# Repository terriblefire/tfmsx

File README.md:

# TFMSX

A homebrew MSX2 machine using as many of the original chips as possible, with custom CPLD logic to implement the MSX slot system, memory mapper, and bus interface.

## Discord

Join the TF discord for help 

https://discord.gg/Q5zfusgnmH 

## Overview

TFMSX is an open-source hardware implementation of the MSX2 standard that combines authentic MSX chips (VDP, PSG, CPU) with modern programmable logic. The design uses a Xilinx XC95288XL CPLD to handle:

- MSX slot system (4 primary slots + secondary slot expansion)
- Memory mapper (512KB SRAM organized as 32 pages of 16KB)
- I/O address decoding and bus arbitration
- Clock generation and distribution
- Real-time clock (RP5C01A) interface

## Features

- **MSX2 Compatible**: Full MSX2 slot architecture with expansion capability
- **Original Components**: Uses genuine Yamaha V9958 VDP, YM2149 PSG, Z80 CPU
- **512KB RAM**: Memory mapper providing 32 banks of 16KB
- **Real-time Clock**: RP5C01A battery-backed RTC
- **Expansion Slots**: Support for cartridges and expansion boards
- **Multiple Revisions**: Hardware evolved through rev0 → rev1 → rev2 with improvements
- **Comprehensive Testing**: Automated test suite with CI/CD integration

## Hardware Revisions

The current repository contains the **Rev 2** design (see `boards/tfmsxr2/`), which includes:

- Improved audio output and PSG interface
- VDP reset control
- SRAM write enable (SWR pin)
- Fixed WAIT signal generation for proper Z80 timing
- Corrected slot select logic

Previous hardware revisions (Rev 0, Rev 1) are documented in the Eagle design files under `eagle/tfmsx_rev*.brd/sch`.

## Repository Structure

```
tfmsx/
├── rtl/                    # Verilog RTL source code
│   ├── tfmsx_top.v        # Top-level CPLD module
│   ├── clocks.v           # Clock generation (CPU, PSG, slot clocks)
│   └── rp5c01a.v          # Real-time clock module
├── boards/                 # Board-specific build configurations
│   ├── tfmsxr2/           # Revision 2 board (current)
│   ├── Makefile.cpld      # Common CPLD build rules
│   ├── Makefile.inc       # Docker/Xilinx environment setup
│   └── boards.txt         # List of board configurations
├── testsuite/             # Verification test benches
│   ├── bus/               # Bus interface tests (SRAM, ROM, VDP, PSG, slots)
│   │   ├── test_sram_access.v    # SRAM read/write tests
│   │   ├── test_rom_access.v     # ROM access tests
│   │   ├── test_vdp_io.v         # VDP I/O tests
│   │   ├── test_psg_io.v         # PSG I/O tests
│   │   ├── test_slot_access.v    # Slot system tests
│   │   ├── bus_fixture.vinc      # Common test fixture
│   │   ├── bus_tasks.vinc        # Reusable bus cycle tasks
│   │   └── Makefile              # Test build rules
│   ├── rtl/               # Simulation support files (Xilinx primitives)
│   ├── clocks.vinc        # Clock generation for tests
│   ├── unittest.vinc      # Test assertion macros
│   └── Makefile.inc       # Common test environment setup
├── eagle/                 # Eagle CAD hardware designs
│   ├── tfmsx.sch/.brd     # Main board schematic and layout
│   ├── extract_bom.py     # BOM extraction script
│   └── Makefile           # Automated Gerber/PDF/BOM generation
├── roms/                  # MSX system ROM tools
│   ├── Makefile           # Automated ROM download and assembly
│   └── makedefaultroms.sh # Legacy script (deprecated)
└── .github/workflows/        # CI/CD automation
    ├── run-tests.yml         # Automated test execution
    ├── gerbers.yml           # Gerber file generation
    ├── schematic-pdf.yml     # PDF schematic generation
    └── generate_assembly.yml # BOM and CPL generation
```

## Building the CPLD Firmware

### Prerequisites

- **Linux**: Xilinx ISE 10.1 installed at `/opt/Xilinx/10.1/`
- **macOS/Windows**: Docker (automatically builds and uses container)

The build system automatically handles Docker on non-Linux platforms.

### Build All Boards

```bash
cd boards
make all
```

This compiles CPLD firmware for all boards listed in `boards/boards.txt` and generates `.jed` JEDEC programming files.

### Build Specific Board

```bash
cd boards/tfmsxr2
make
```

Output: `tfmsxr2_top.jed` (JEDEC programming file) and `tfmsxr2_top.svf` (Serial Vector Format)

### Clean Build Artifacts

```bash
cd boards
make clean       # Remove intermediate build files
make distclean   # Remove all generated files including .jed
```

### Create Release Package

```bash
cd boards
make zip
```

Generates: `tfmsx_YYYY_MM_DD_<git-hash>.zip` containing all board `.jed` files.

## Programming the CPLD

Flash the CPLD using xc3sprog with an FT232H-based programmer:

```bash
cd boards/tfmsxr2
make flash
```

This requires:
- xc3sprog tool installed
- FT232H USB programmer connected
- Proper JTAG connections to the XC95288XL

## MSX System ROMs

The `roms/` directory contains a Makefile to download and prepare MSX2 system ROMs for use with the TFMSX hardware.

### Building System ROMs

```bash
cd roms
make           # Download ROMs and create default.rom
make -j8       # Parallel download (faster)
make clean     # Remove all generated files
```

The Makefile automatically downloads MSX2 BIOS ROMs from the BlueMSX emulator repository and creates a combined ROM image with multiple banks:

- **Bank 0**: MSX2 (Standard) + MSX2EXT + DISK ROM
- **Bank 1**: MSX2BR (Brazilian) + MSX2BREXT + DISK ROM
- **Bank 2**: MSX2P (MSX2+) + MSX2PEXT + DISK ROM
- **Bank 3**: MSX2SP (Spanish MSX2+) + MSX2SPEXT + DISK ROM

The final output is `default.rom`, which contains all four banks concatenated together. This allows the TFMSX hardware to support multiple MSX2 configurations by bank switching.

**Features**:
- Dependency tracking: Only downloads missing files
- Incremental builds: Only rebuilds changed targets
- Parallel downloads: Use `-j` flag for faster downloads
- Clean target: Easy cleanup with `make clean`

**Note**: These ROMs are copyrighted by their respective manufacturers. Only links are provided. 

## Technical Details

### Memory Map

| Address Range | Function |
|---------------|----------|
| 0x0000-0x3FFF | Page 0 (slot configurable) |
| 0x4000-0x7FFF | Page 1 (slot configurable) |
| 0x8000-0xBFFF | Page 2 (slot configurable) |
| 0xC000-0xFFFF | Page 3 (slot configurable) |

Each page can be mapped to any of 4 slots via the slot register (I/O port 0xA8).

### I/O Port Map

| Port(s) | Device | Function |
|---------|--------|----------|
| 0x98-0x9B | VDP | Yamaha V9958 Video Display Processor |
| 0xA0-0xA3 | PSG | Yamaha YM2149 Programmable Sound Generator |
| 0xA8-0xAB | PPI | 8255 Programmable Peripheral Interface (slot register) |
| 0xB4 | RTC | RP5C01A address latch |
| 0xB5 | RTC | RP5C01A data register |
| 0xFC-0xFF | Mapper | Memory mapper page registers (32 banks × 16KB) |

### Clock Frequencies

- **Master Clock**: 28 MHz (crystal oscillator)
- **CPU Clock (CLKCPU)**: 3.5 MHz (÷8)
- **PSG Clock (PSGCLK)**: 1.75 MHz (÷16)
- **Slot Clock (SLOTCLK)**: 3.5 MHz (÷8)

### CPLD Resources

- **Target Device**: Xilinx XC95288XL-10-TQ144
- **Macrocells**: 288
- **Package**: 144-pin TQFP
- **Speed Grade**: -10 (100 MHz)

Utilization varies by revision but typically uses 70-85% of available macrocells.

## Testing

The `testsuite/` directory contains Verilog testbenches for verifying CPLD functionality. Tests use Icarus Verilog for simulation.

### Running Tests

```bash
cd testsuite/bus
make              # Run all tests
make clean        # Clean generated files
```

### Test Coverage

The test suite includes comprehensive coverage of bus operations:

- **test_sram_access.v**: SRAM read/write operations, chip select timing, mapper control
- **test_rom_access.v**: ROM output enable, address decoding, data bus behavior
- **test_vdp_io.v**: VDP I/O ports (0x98-0x9B), read/write signals, timing
- **test_psg_io.v**: PSG I/O ports (0xA0-0xA2), control signals
- **test_slot_access.v**: MSX slot system, memory mapping, slot registers (0xA8, 0xFC-0xFF)

Each test verifies:
- Correct signal timing and activation
- Proper address decoding
- Bus protocol compliance
- Memory/peripheral access patterns

Tests automatically generate waveform files (`.vcd`) for debugging.

### Continuous Integration

All tests run automatically on push via GitHub Actions. Test status is visible in the badge at the top of this README.

## Development Workflow

1. **Modify RTL**: Edit Verilog files in `rtl/`
2. **Run Tests**: `cd testsuite/bus && make` to verify changes (see [Testing](#testing) section)
3. **Build CPLD**: `cd boards/tfmsxr2 && make`
4. **Flash Hardware**: `make flash` (if hardware available)
5. **Test on Hardware**: Verify functionality on physical board

## VDP Configuration

The TFMSX board supports both V9938 and V9958 video display processors. The VDP chip type is selected using jumpers JP3 and JP4. The CPLD automatically handles all other configuration differences.

### Jumper Settings

| VDP Chip | JP3 (Single Position) | JP4 (Two Position) |
|----------|----------------------|-------------------|
| **V9938** | **Closed** | **Left Position** |
| **V9958** | **Open** | **Right Position** |

**Jumper Types**:
- **JP3**: Single position jumper - either closed (jumper installed) or open (no jumper)
- **JP4**: Two position jumper - set to either left or right position

**Configuration Summary**:
- **V9938**: JP3 closed, JP4 left position
- **V9958**: JP3 open, JP4 right position

The CPLD logic uses these jumper settings to configure timing and control signals appropriately for the installed VDP chip.

## Hardware Design Files

Eagle CAD schematics and board layouts are in `eagle/`:

- **Main Board**: `tfmsx.sch` / `tfmsx.brd` (Rev 2 - current design)
- **Previous Revisions**: `tfmsx_rev0.*`, `tfmsx_rev1.*` (historical reference)

### Generating Gerber Files

The `eagle/` directory includes a Makefile for automated Gerber generation using Docker (no Eagle installation required).

```bash
cd eagle
make               # Generate Gerbers for main TFMSX board
make pdf           # Generate PDF schematic for main board
make bom           # Generate Bill of Materials (BOM) CSV
make cpl           # Generate Component Placement List (CPL) CSV
make assembly      # Generate both BOM and CPL for assembly
```

Output files are named with git commit hash and date (e.g., `tfmsx_a1b2c3d_2025_11_14.zip`).

**Requirements**:
- Docker with `terriblefire78/eagle:v1` and `terriblefire78/eagle-pdf` images (for gerbers and PDF)
- Python 3 (for BOM/CPL generation)

### Assembly Files (BOM and CPL)

Generate assembly files for PCB fabrication and assembly:

```bash
cd eagle
make assembly      # Generate both BOM and CPL
```

This creates two files for JLCPCB/PCBA services:

**BOM (`tfmsx_bom.csv`)** contains:
- **Comment**: Component value/part number
- **Designator**: Reference designators (e.g., C1, C2, R5)
- **Footprint**: PCB footprint package
- **LCSC Part #**: LCSC/JLCPCB part number (if available)

**CPL (`tfmsx_cpl.csv`)** contains:
- **Designator**: Component reference
- **Mid X, Mid Y**: Component center position in mm
- **Layer**: Top or Bottom
- **Rotation**: Component rotation in degrees

The BOM groups identical components together for easy ordering and assembly.

## Contributing

This is an open hardware project. Contributions welcome for:

- RTL improvements and optimizations
- Additional test coverage (please include tests for new features)
- Hardware revision suggestions
- Documentation enhancements
- Bug fixes

When contributing RTL changes, please ensure all tests pass by running `cd testsuite/bus && make`.

## License

This work is licensed under the Creative Commons Attribution-NoDerivatives 4.0 International License.

Copyright (c) 2021-2025 Stephen J. Leary

You are free to:
- **Share** - copy and redistribute the material in any medium or format for any purpose, even commercially

Under the following terms:
- **Attribution** - You must give appropriate credit, provide a link to the license, and indicate if changes were made
- **NoDerivatives** - If you remix, transform, or build upon the material, you may not distribute the modified material

See the [LICENSE](LICENSE) file for the complete license text, or visit:
https://creativecommons.org/licenses/by-nd/4.0/

## References

- [MSX Technical Documentation](https://www.msx.org/)
- [MSX Resource Center](https://www.msx.org/wiki/)
- MSX2 Technical Handbook
- Z80 CPU User Manual
- [Yamaha V9958 VDP Documentation](https://www.msx.org/wiki/Yamaha_V9958)

## Contact

For questions, issues, or contributions, please use the GitHub issue tracker.

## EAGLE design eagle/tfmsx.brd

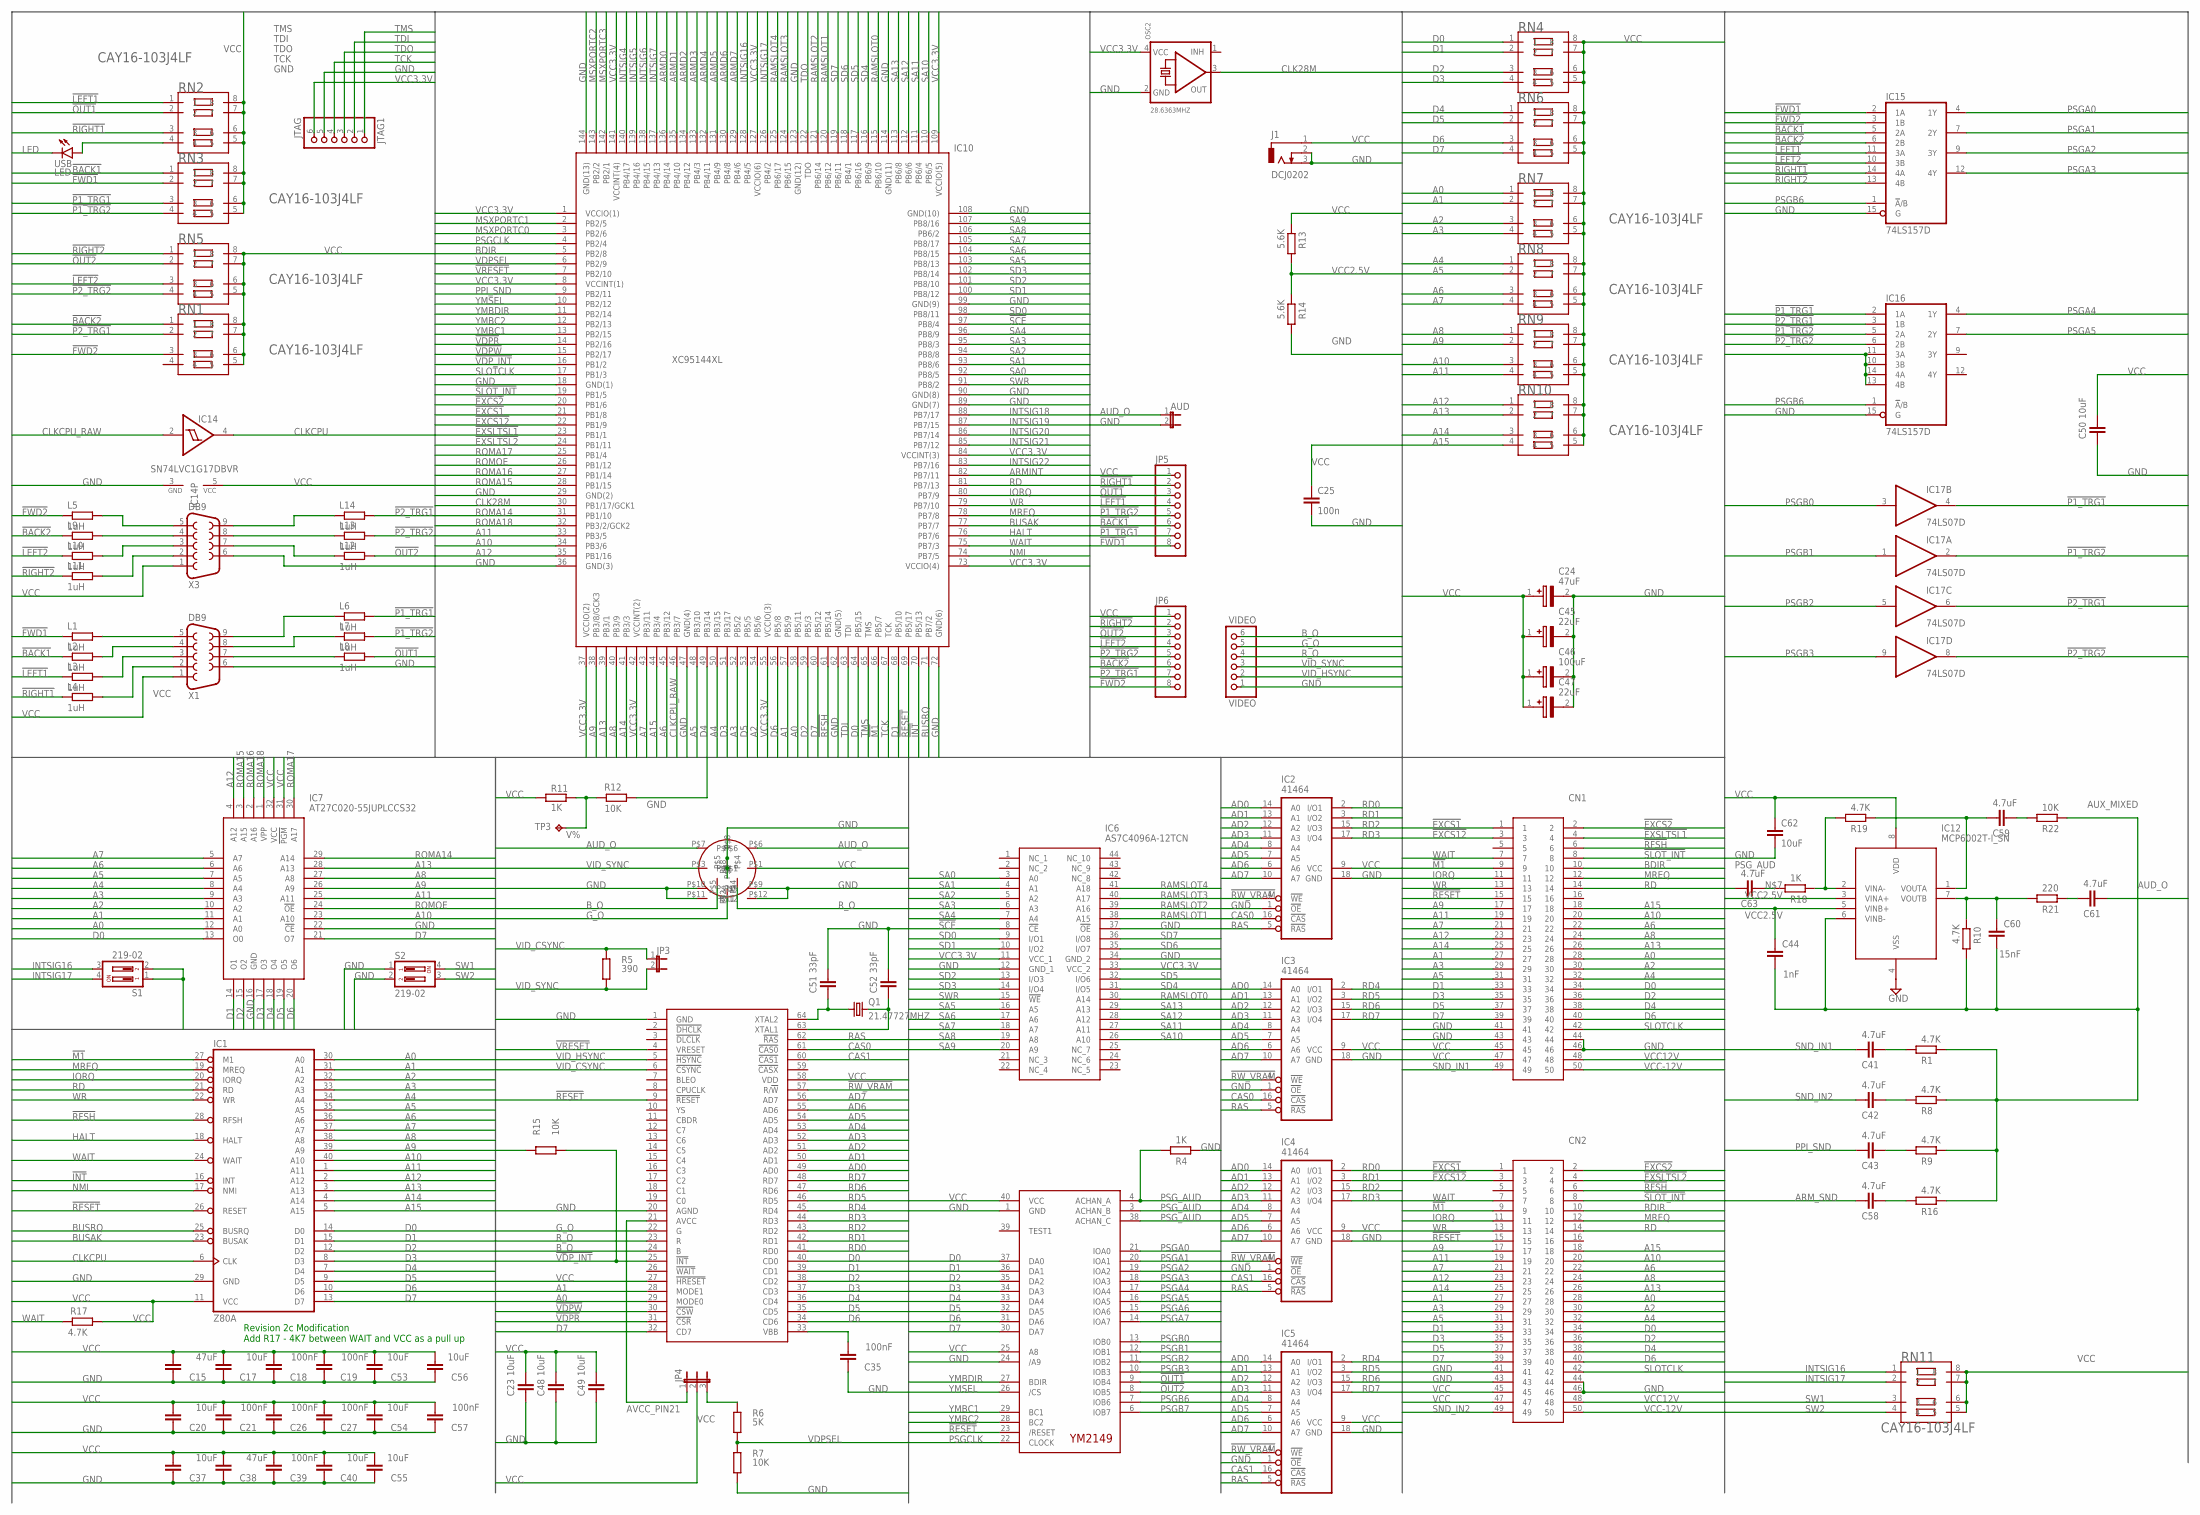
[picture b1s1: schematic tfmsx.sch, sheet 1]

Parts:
AUD: JUMPER-2PTH; 1X02
C15, C38: 47uF; C1206
C17, C20, C23, C37, C40, C48, C49, C50, C53, C54, C55, C56, C62: 10uF; C1206
C18, C19, C21, C26, C27, C35, C39, C57: 100nF; C1206
C24: 47uF; CAPAE430X550N
C25: 100n; C0603
C41, C42, C43, C58, C59, C61, C63: 4.7uF; C0603
C44: 1nF; C0603
C45, C47: 22uF; CAPAE430X550N
C46: 100uF; CAPAE430X550N
C51, C52: 33pF; C0805
C60: 15nF; C0603
CN1, CN2: 5530843-5; 55308435
IC1: Z80A; DIL40
IC2, IC3, IC4, IC5: 41464; DIL18
IC6: AS7C4096A-12TCN; SOP80P1181X120-44N
IC7: AT27C020-55JUPLCCS32; PLCC-S32
IC9: VDP9958; SOT274
IC10: XC95144XL; SAMACSYS_PARTS_QFP50P2200X2200X160-144N
IC12: MCP6002T-I_SN; SOIC127P600X175-8N
IC13: YM2149; DIL40
IC14: SN74LVC1G17DBVR; SOT23-5
IC15, IC16: 74LS157D; SO16
IC17: 74LS07D; SO14
J1: DCJ0202
JP3: JP1E; JP1
JP4: JP2E; JP2
JP5, JP6: HEADER-1X8ROUND; 1X08_ROUND
JTAG1: JTAG; 1X06_ROUND
L1, L2, L3, L4, L5, L6, L7, L8, L9, L10, L11, L12, L13, L14: 1uH; R1206
OSC2: 28.6363MHZ; OSC_7X5MM
Q1: 21.47727MHZ; HC49/S
R1, R8, R9, R10, R16, R17, R19: 4.7K; M0805
R4, R11, R18: 1K; M0805
R5: 390; M0805
R6: 5K; M0805
R7, R12, R15, R22: 10K; M0805
R13, R14: 5.6K; M0805
R21: 220; M0805
RN1, RN2, RN3, RN4, RN5, RN6, RN7, RN8, RN9, RN10, RN11: CAY16-103J4LF; RESCAXE80P320X160-8N
S1, S2: 219-02; CTS-219-02
TP3: TPB1,27; B1,27
U$3: DIN45326; 838_DIN8
USB: LED; SML0805
VIDEO: VIDEO; 1X06_ROUND
X1, X3: DB9; F09HP

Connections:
!BACK1: IC15.5 (2A), JP5.6, L2.1, RN3.1; also elsewhere on the board
!BACK1_B: L2.2, X1.4
!BACK2: IC15.6 (2B), JP6.6, L9.1, RN1.1
!EXCS1: CN1.1, CN2.1, IC10.21 (PB1/8)
!EXCS2: CN1.2, CN2.2, IC10.20 (PB1/6)
!EXCS12: CN1.3, CN2.3, IC10.22 (PB1/9)
!EXSLTSL1: CN1.4, IC10.23 (PB1/1)
!EXSLTSL2: CN2.4, IC10.24 (PB1/11)
!FWD1: IC15.2 (1A), JP5.8, L1.1, RN3.2; also elsewhere on the board
!FWD1_B: L1.2, X1.5
!FWD2: IC15.3 (1B), JP6.8, L5.1, RN1.3
!INT: IC1.16 (INT), IC10.70 (PB5/13)
!LEFT1: IC15.11 (3A), JP5.4, L3.1, RN2.1; also elsewhere on the board
!LEFT1_B: L3.2, X1.3
!LEFT2: IC15.10 (3B), JP6.4, L10.1, RN5.3
!M1: CN1.9, CN2.9, IC1.27 (M1), IC10.66 (PB5/7)
!OUT1: IC13.9 (IOB4), JP5.3, L8.2, RN2.2; also elsewhere on the board
!OUT2: IC13.8 (IOB5), JP6.3, L12.2, RN5.2
!P1_TRG1: IC16.2 (1A), IC17.4 (O), JP5.7, L6.2, RN3.3; also elsewhere on the board
!P1_TRG2: IC16.5 (2A), IC17.2 (O), JP5.5, L7.2, RN3.4; also elsewhere on the board
!P2_TRG1: IC16.3 (1B), IC17.6 (O), JP6.7, L14.2, RN1.2
!P2_TRG2: IC16.6 (2B), IC17.8 (O), JP6.5, L13.2, RN5.4
!RESET: CN1.15, CN2.15, IC1.26 (RESET), IC9.9 (!RESET), IC10.69 (PB5/17), IC13.23 (/RESET)
!RFSH: CN1.6, CN2.6, IC1.28 (RFSH), IC10.61 (PB5/14)
!RIGHT1: IC15.14 (4A), JP5.2, L4.1, RN2.3; also elsewhere on the board
!RIGHT1_B: L4.2, X1.2
!RIGHT2: IC15.13 (4B), JP6.2, L11.1, RN5.1
!RW_VRAM: IC2.4 (!WE), IC3.4 (!WE), IC4.4 (!WE), IC5.4 (!WE), IC9.57 (R/!W)
!SCE: IC6.8 (!CE), IC10.97 (PB8/4)
!SLOT_INT: CN1.8, CN2.8, IC10.19 (PB1/5)
!VDPR: IC9.31 (!CSR), IC10.14 (PB2/16)
!VDPW: IC9.30 (!CSW), IC10.15 (PB2/17)
!VDP_INT: IC9.25 (!INT), IC10.16 (PB1/2), R15.1
!VRESET: IC9.4 (VRESET), IC10.7 (PB2/10)
A0: CN1.28, CN2.28, IC1.30 (A0), IC7.12 (A0), IC9.29 (MODE0), IC10.58 (PB5/11), RN7.1
A1: CN1.27, CN2.27, IC1.31 (A1), IC7.11 (A1), IC9.28 (MODE1), IC10.57 (PB5/9), RN7.2
A2: CN1.30, CN2.30, IC1.32 (A2), IC7.10 (A2), IC10.54 (PB5/6), RN7.3
A3: CN1.29, CN2.29, IC1.33 (A3), IC7.9 (A3), IC10.52 (PB5/2), RN7.4
A4: CN1.32, CN2.32, IC1.34 (A4), IC7.8 (A4), IC10.50 (PB3/15), RN8.1
A5: CN1.31, CN2.31, IC1.35 (A5), IC7.7 (A5), IC10.48 (PB3/10), RN8.2
A6: CN1.22, CN2.22, IC1.36 (A6), IC7.6 (A6), IC10.45 (PB3/12), RN8.3
A7: CN1.21, CN2.21, IC1.37 (A7), IC7.5 (A7), IC10.43 (PB3/11), RN8.4
A8: CN1.24, CN2.24, IC1.38 (A8), IC7.27 (A8), IC10.40 (PB3/9), RN9.1
A9: CN1.17, CN2.17, IC1.39 (A9), IC7.26 (A9), IC10.38 (PB3/8/GCK3), RN9.2
A10: CN1.20, CN2.20, IC1.40 (A10), IC7.23 (A10), IC10.34 (PB3/6), RN9.3
A11: CN1.19, CN2.19, IC1.1 (A11), IC7.25 (A11), IC10.33 (PB3/5), RN9.4
A12: CN1.23, CN2.23, IC1.2 (A12), IC7.4 (A12), IC10.35 (PB1/16), RN10.1
A13: CN1.26, CN2.26, IC1.3 (A13), IC7.28 (A13), IC10.39 (PB3/1), RN10.2
A14: CN1.25, CN2.25, IC1.4 (A14), IC10.41 (PB3/3), RN10.3
A15: CN1.18, CN2.18, IC1.5 (A15), IC10.44 (PB3/4), RN10.4
AD0: IC2.14 (A0), IC3.14 (A0), IC4.14 (A0), IC5.14 (A0), IC9.49 (AD0)
AD1: IC2.13 (A1), IC3.13 (A1), IC4.13 (A1), IC5.13 (A1), IC9.50 (AD1)
AD2: IC2.12 (A2), IC3.12 (A2), IC4.12 (A2), IC5.12 (A2), IC9.51 (AD2)
AD3: IC2.11 (A3), IC3.11 (A3), IC4.11 (A3), IC5.11 (A3), IC9.52 (AD3)
AD4: IC2.8 (A4), IC3.8 (A4), IC4.8 (A4), IC5.8 (A4), IC9.53 (AD4)
AD5: IC2.7 (A5), IC3.7 (A5), IC4.7 (A5), IC5.7 (A5), IC9.54 (AD5)
AD6: IC2.6 (A6), IC3.6 (A6), IC4.6 (A6), IC5.6 (A6), IC9.55 (AD6)
AD7: IC2.10 (A7), IC3.10 (A7), IC4.10 (A7), IC5.10 (A7), IC9.56 (AD7)
ARMD0: IC10.136 (PB4/14); also elsewhere on the board
ARMD1: IC10.135 (PB4/10); also elsewhere on the board
ARMD2: IC10.134 (PB4/12); also elsewhere on the board
ARMD3: IC10.133 (PB4/3); also elsewhere on the board
ARMD4: IC10.132 (PB4/11); also elsewhere on the board
ARMD5: IC10.131 (PB4/9); also elsewhere on the board
ARMD6: IC10.130 (PB4/8); also elsewhere on the board
ARMD7: IC10.129 (PB4/6); also elsewhere on the board
ARMINT: IC10.82 (PB7/11); also elsewhere on the board
ARM_SND: C58.1; also elsewhere on the board
AUD_O: AUD.1, C61.2, U$3.P$6, U$3.P$7
AUX_MIXED: C44.1, C60.1, IC12.6 (VINB-), R1.1, R8.1, R9.1, R10.2, R16.1, R22.1
AVCC_PIN21: IC9.21 (AVCC), JP4.1
BDIR: CN1.10, CN2.10, IC10.5 (PB2/8)
BUSAK: IC1.23 (BUSAK), IC10.77 (PB7/7)
BUSRQ: IC1.25 (BUSRQ), IC10.71 (PB7/2)
B_O: IC9.24 (B), U$3.P$5, VIDEO.6
CAS0: IC2.16 (!CAS), IC3.16 (!CAS), IC9.61 (!CAS0)
CAS1: IC4.16 (!CAS), IC5.16 (!CAS), IC9.60 (!CAS1)
CLK28M: IC10.30 (PB1/17/GCK1), OSC2.3 (OUT)
CLKCPU: IC1.6 (CLK), IC14.4 (O)
CLKCPU_RAW: IC10.46 (PB3/7), IC14.2 (I)
D0: CN1.34, CN2.34, IC1.14 (D0), IC7.13 (O0), IC9.40 (CD0), IC10.64 (PB5/15), IC13.37 (DA0), RN4.1
D1: CN1.33, CN2.33, IC1.15 (D1), IC7.14 (O1), IC9.39 (CD1), IC10.68 (PB5/10), IC13.36 (DA1), RN4.2
D2: CN1.36, CN2.36, IC1.12 (D2), IC7.15 (O2), IC9.38 (CD2), IC10.59 (PB5/3), IC13.35 (DA2), RN4.3
D3: CN1.35, CN2.35, IC1.8 (D3), IC7.17 (O3), IC9.37 (CD3), IC10.51 (PB3/17), IC13.34 (DA3), RN4.4
D4: CN1.38, CN2.38, IC1.7 (D4), IC7.18 (O4), IC9.36 (CD4), IC10.49 (PB3/14), IC13.33 (DA4), RN6.1
D5: CN1.37, CN2.37, IC1.9 (D5), IC7.19 (O5), IC9.35 (CD5), IC10.53 (PB5/5), IC13.32 (DA5), RN6.2
D6: CN1.40, CN2.40, IC1.10 (D6), IC7.20 (O6), IC9.34 (CD6), IC10.56 (PB5/8), IC13.31 (DA6), RN6.3
D7: CN1.39, CN2.39, IC1.13 (D7), IC7.21 (O7), IC9.32 (CD7), IC10.60 (PB5/12), IC13.30 (DA7), RN6.4
GND: AUD.2, C15.1, C17.1, C18.1, C19.1, C20.1, C21.1, C23.1, C24.2 (-), C25.2, C26.1, C27.1, C35.1, C37.1, C38.1, C39.1, C40.1, C45.2 (-), C46.2 (-), C47.2 (-), C48.1, C49.1, C50.1, C51.2, C52.2, C53.1, C54.1, C55.1, C56.1, C57.1, C62.2, CN1.41, CN1.43, CN1.44, CN1.46, CN2.41, CN2.43, CN2.44, CN2.46, IC1.29 (GND), IC2.1 (!OE), IC2.18 (GND), IC3.1 (!OE), IC3.18 (GND), IC4.1 (!OE), IC4.18 (GND), IC5.1 (!OE), IC5.18 (GND), IC6.12 (GND_1), IC6.34 (GND_2), IC6.37 (!OE), IC7.16 (GND), IC7.22 (!CE), IC9.1 (GND), IC9.20 (AGND), IC10.18 (GND(1)), IC10.29 (GND(2)), IC10.36 (GND(3)), IC10.47 (GND(4)), IC10.62 (GND(5)), IC10.72 (GND(6)), IC10.89 (GND(7)), IC10.90 (GND(8)), IC10.99 (GND(9)), IC10.108 (GND(10)), IC10.114 (GND(11)), IC10.123 (GND(12)), IC10.144 (GND(13)), IC12.4 (VSS), IC13.1 (GND), IC13.24 (/A9), IC14.3 (GND), IC15.8 (GND), IC15.15 (G), IC16.8 (GND), IC16.10 (3B), IC16.11 (3A), IC16.13 (4B), IC16.14 (4A), IC16.15 (G), IC17.7 (GND), J1.2, J1.3, JTAG1.5, OSC2.2 (GND), R4.1, R7.1, R12.1, R14.2, S1.1, S1.2, S2.1, S2.2, U$3.P$8, U$3.P$9, U$3.P$10, U$3.P$11, U$3.P$12, VIDEO.1, X1.6, X3.6; also elsewhere on the board
G_O: IC9.22 (G), U$3.P$2, VIDEO.5
HALT: IC1.18 (HALT), IC10.76 (PB7/6)
INTSIG4: IC10.140 (PB4/17); also elsewhere on the board
INTSIG5: IC10.139 (PB4/16); also elsewhere on the board
INTSIG6: IC10.138 (PB4/15); also elsewhere on the board
INTSIG7: IC10.137 (PB4/13); also elsewhere on the board
INTSIG16: IC10.128 (PB4/5), RN11.1, S1.3; also elsewhere on the board
INTSIG17: IC10.126 (PB4/2), RN11.2, S1.4; also elsewhere on the board
INTSIG18: IC10.88 (PB7/17); also elsewhere on the board
INTSIG19: IC10.87 (PB7/15); also elsewhere on the board
INTSIG20: IC10.86 (PB7/14); also elsewhere on the board
INTSIG21: IC10.85 (PB7/12); also elsewhere on the board
INTSIG22: IC10.83 (PB7/16); also elsewhere on the board
IORQ: CN1.11, CN2.11, IC1.20 (IORQ), IC10.80 (PB7/9)
LED: USB.C; also elsewhere on the board
MREQ: CN1.12, CN2.12, IC1.19 (MREQ), IC10.78 (PB7/8)
MSXPORTC0: IC10.3 (PB2/6); also elsewhere on the board
MSXPORTC1: IC10.2 (PB2/5); also elsewhere on the board
MSXPORTC2: IC10.143 (PB2/2); also elsewhere on the board
MSXPORTC3: IC10.142 (PB2/1); also elsewhere on the board
unnamed: C51.1, IC9.64 (XTAL2), Q1.1
unnamed: C52.1, IC9.63 (XTAL1), Q1.2
unnamed: C35.2, IC9.33 (VBB)
unnamed: L8.1, X1.7
unnamed: L7.1, X1.8
unnamed: L6.1, X1.9
unnamed: C63.2, R18.2
unnamed: L9.2, X3.4
unnamed: L10.2, X3.3
unnamed: L11.2, X3.2
unnamed: L5.2, X3.5
unnamed: L12.1, X3.7
unnamed: L13.1, X3.8
unnamed: L14.1, X3.9
unnamed: RN2.4, USB.A
unnamed: C41.2, R1.2
unnamed: C42.2, R8.2
unnamed: C43.2, R9.2
unnamed: C58.2, R16.2
unnamed: JP4.3, R6.2
unnamed: IC12.2 (VINA-), R18.1, R19.2
unnamed: C59.1, IC12.1 (VOUTA), R19.1
unnamed: C59.2, R22.2
unnamed: C60.2, IC12.7 (VOUTB), R10.1, R21.2
unnamed: C61.1, R21.1
NMI: IC1.17 (NMI), IC10.74 (PB7/5)
PPI_SND: C43.1, IC10.9 (PB2/11)
PSGA0: IC13.21 (IOA0), IC15.4 (1Y)
PSGA1: IC13.20 (IOA1), IC15.7 (2Y)
PSGA2: IC13.19 (IOA2), IC15.9 (3Y)
PSGA3: IC13.18 (IOA3), IC15.12 (4Y)
PSGA4: IC13.17 (IOA4), IC16.4 (1Y)
PSGA5: IC13.16 (IOA5), IC16.7 (2Y)
PSGA6: IC13.15 (IOA6)
PSGA7: IC13.14 (IOA7)
PSGB0: IC13.13 (IOB0), IC17.3 (I)
PSGB1: IC13.12 (IOB1), IC17.1 (I)
PSGB2: IC13.11 (IOB2), IC17.5 (I)
PSGB3: IC13.10 (IOB3), IC17.9 (I)
PSGB6: IC13.7 (IOB6), IC15.1 (!A!/B), IC16.1 (!A!/B)
PSGB7: IC13.6 (IOB7)
PSGCLK: IC10.4 (PB2/4), IC13.22 (CLOCK)
PSG_AUD: C63.1, IC13.3 (ACHAN_B), IC13.4 (ACHAN_A), IC13.38 (ACHAN_C), R4.2
RAMSLOT0: IC6.30 (A14), IC10.115 (PB6/10)
RAMSLOT1: IC6.38 (A15), IC10.120 (PB6/12)
RAMSLOT2: IC6.39 (A16), IC10.121 (PB6/14)
RAMSLOT3: IC6.40 (A17), IC10.124 (PB6/15)
RAMSLOT4: IC6.41 (A18), IC10.125 (PB6/17)
RAS: IC2.5 (!RAS), IC3.5 (!RAS), IC4.5 (!RAS), IC5.5 (!RAS), IC9.62 (!RAS)
RD: CN1.14, CN2.14, IC1.21 (RD), IC10.81 (PB7/13)
RD0: IC2.2 (I/O1), IC4.2 (I/O1), IC9.41 (RD0)
RD1: IC2.3 (I/O2), IC4.3 (I/O2), IC9.42 (RD1)
RD2: IC2.15 (I/O3), IC4.15 (I/O3), IC9.43 (RD2)
RD3: IC2.17 (I/O4), IC4.17 (I/O4), IC9.44 (RD3)
RD4: IC3.2 (I/O1), IC5.2 (I/O1), IC9.45 (RD4)
RD5: IC3.3 (I/O2), IC5.3 (I/O2), IC9.46 (RD5)
RD6: IC3.15 (I/O3), IC5.15 (I/O3), IC9.47 (RD6)
RD7: IC3.17 (I/O4), IC5.17 (I/O4), IC9.48 (RD7)
ROMA14: IC7.29 (A14), IC10.31 (PB1/10)
ROMA15: IC7.3 (A15), IC10.28 (PB1/15)
ROMA16: IC7.2 (A16), IC10.27 (PB1/14)
ROMA17: IC7.30 (A17), IC10.25 (PB1/4)
ROMA18: IC7.1 (VPP), IC10.32 (PB3/2/GCK2)
ROMOE: IC7.24 (!OE), IC10.26 (PB1/12)
R_O: IC9.23 (R), U$3.P$4, VIDEO.4
SA0: IC6.3 (A0), IC10.92 (PB8/5)
SA1: IC6.4 (A1), IC10.93 (PB8/6)
SA2: IC6.5 (A2), IC10.94 (PB8/8)
SA3: IC6.6 (A3), IC10.95 (PB8/3)
SA4: IC6.7 (A4), IC10.96 (PB8/9)
SA5: IC6.16 (A5), IC10.103 (PB8/13)
SA6: IC6.17 (A6), IC10.104 (PB8/15)
SA7: IC6.18 (A7), IC10.105 (PB8/17)
SA8: IC6.19 (A8), IC10.106 (PB6/2)
SA9: IC6.20 (A9), IC10.107 (PB8/16)
SA10: IC6.26 (A10), IC10.110 (PB6/5)
SA11: IC6.27 (A11), IC10.111 (PB6/4)
SA12: IC6.28 (A12), IC10.112 (PB6/6)
SA13: IC6.29 (A13), IC10.113 (PB6/8)
SD0: IC6.9 (I/O1), IC10.98 (PB8/11)
SD1: IC6.10 (I/O2), IC10.100 (PB8/12)
SD2: IC6.13 (I/O3), IC10.101 (PB8/10)
SD3: IC6.14 (I/O4), IC10.102 (PB8/14)
SD4: IC6.31 (I/O5), IC10.116 (PB6/9)
SD5: IC6.32 (I/O6), IC10.117 (PB6/16)
SD6: IC6.35 (I/O7), IC10.118 (PB4/1)
SD7: IC6.36 (I/O8), IC10.119 (PB6/11)
SLOTCLK: CN1.42, CN2.42, IC10.17 (PB1/3)
SND_IN1: C41.1, CN1.49
SND_IN2: C42.1, CN2.49
SW1: RN11.3, S2.4; also elsewhere on the board
SW2: RN11.4, S2.3; also elsewhere on the board
SWR: IC6.15 (!WE), IC10.91 (PB8/2)
TCK: IC10.67 (TCK), JTAG1.4
TDI: IC10.63 (TDI), JTAG1.2
TDO: IC10.122 (TDO), JTAG1.3
TMS: IC10.65 (TMS), JTAG1.1
V%: R11.1, R12.2, TP3.TP
VCC: C15.2, C17.2, C18.2, C19.2, C20.2, C21.2, C23.2, C24.1 (+), C25.1, C26.2, C27.2, C37.2, C38.2, C39.2, C40.2, C45.1 (+), C46.1 (+), C47.1 (+), C48.2, C49.2, C50.2, C53.2, C54.2, C55.2, C56.2, C57.2, C62.1, CN1.45, CN1.47, CN2.45, CN2.47, IC1.11 (VCC), IC2.9 (VCC), IC3.9 (VCC), IC4.9 (VCC), IC5.9 (VCC), IC7.31 (!PGM), IC7.32 (VCC), IC9.27 (!HRESET), IC9.58 (VDD), IC12.8 (VDD), IC13.25 (A8), IC13.40 (VCC), IC14.5 (VCC), IC15.16 (VCC), IC16.16 (VCC), IC17.14 (VCC), J1.1, JP4.2, JP5.1, JP6.1, R11.2, R13.1, R15.2, R17.2, RN1.5, RN1.6, RN1.7, RN1.8, RN2.5, RN2.6, RN2.7, RN2.8, RN3.5, RN3.6, RN3.7, RN3.8, RN4.5, RN4.6, RN4.7, RN4.8, RN5.5, RN5.6, RN5.7, RN5.8, RN6.5, RN6.6, RN6.7, RN6.8, RN7.5, RN7.6, RN7.7, RN7.8, RN8.5, RN8.6, RN8.7, RN8.8, RN9.5, RN9.6, RN9.7, RN9.8, RN10.5, RN10.6, RN10.7, RN10.8, RN11.5, RN11.6, RN11.7, RN11.8, U$3.P$1, X1.1, X3.1; also elsewhere on the board
VCC2.5V: C44.2, IC12.3 (VINA+), IC12.5 (VINB+), R13.2, R14.1
VCC3.3V: IC6.11 (VCC_1), IC6.33 (VCC_2), IC10.1 (VCCIO(1)), IC10.8 (VCCINT(1)), IC10.37 (VCCIO(2)), IC10.42 (VCCINT(2)), IC10.55 (VCCIO(3)), IC10.73 (VCCIO(4)), IC10.84 (VCCINT(3)), IC10.109 (VCCIO(5)), IC10.127 (VCCIO(6)), IC10.141 (VCCINT(4)), JTAG1.6, OSC2.4 (VCC); also elsewhere on the board
VCC12V: CN1.48, CN2.48
VCC-12V: CN1.50, CN2.50
VDPSEL: IC10.6 (PB2/9), R6.1, R7.2
VID_CSYNC: IC9.6 (!CSYNC), JP3.1, R5.2
VID_HSYNC: IC9.5 (!HSYNC), VIDEO.2
VID_SYNC: JP3.2, R5.1, U$3.P$3, VIDEO.3
WAIT: CN1.7, CN2.7, IC1.24 (WAIT), IC10.75 (PB7/3), R17.1
WR: CN1.13, CN2.13, IC1.22 (WR), IC10.79 (PB7/10)
YMBC1: IC10.13 (PB2/15), IC13.29 (BC1)
YMBC2: IC10.12 (PB2/13), IC13.28 (BC2)
YMBDIR: IC10.11 (PB2/14), IC13.27 (BDIR)
YMSEL: IC10.10 (PB2/12), IC13.26 (/CS)

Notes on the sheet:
Revision 2c Modification Add R17 - 4K7 between WAIT and VCC as a pull up

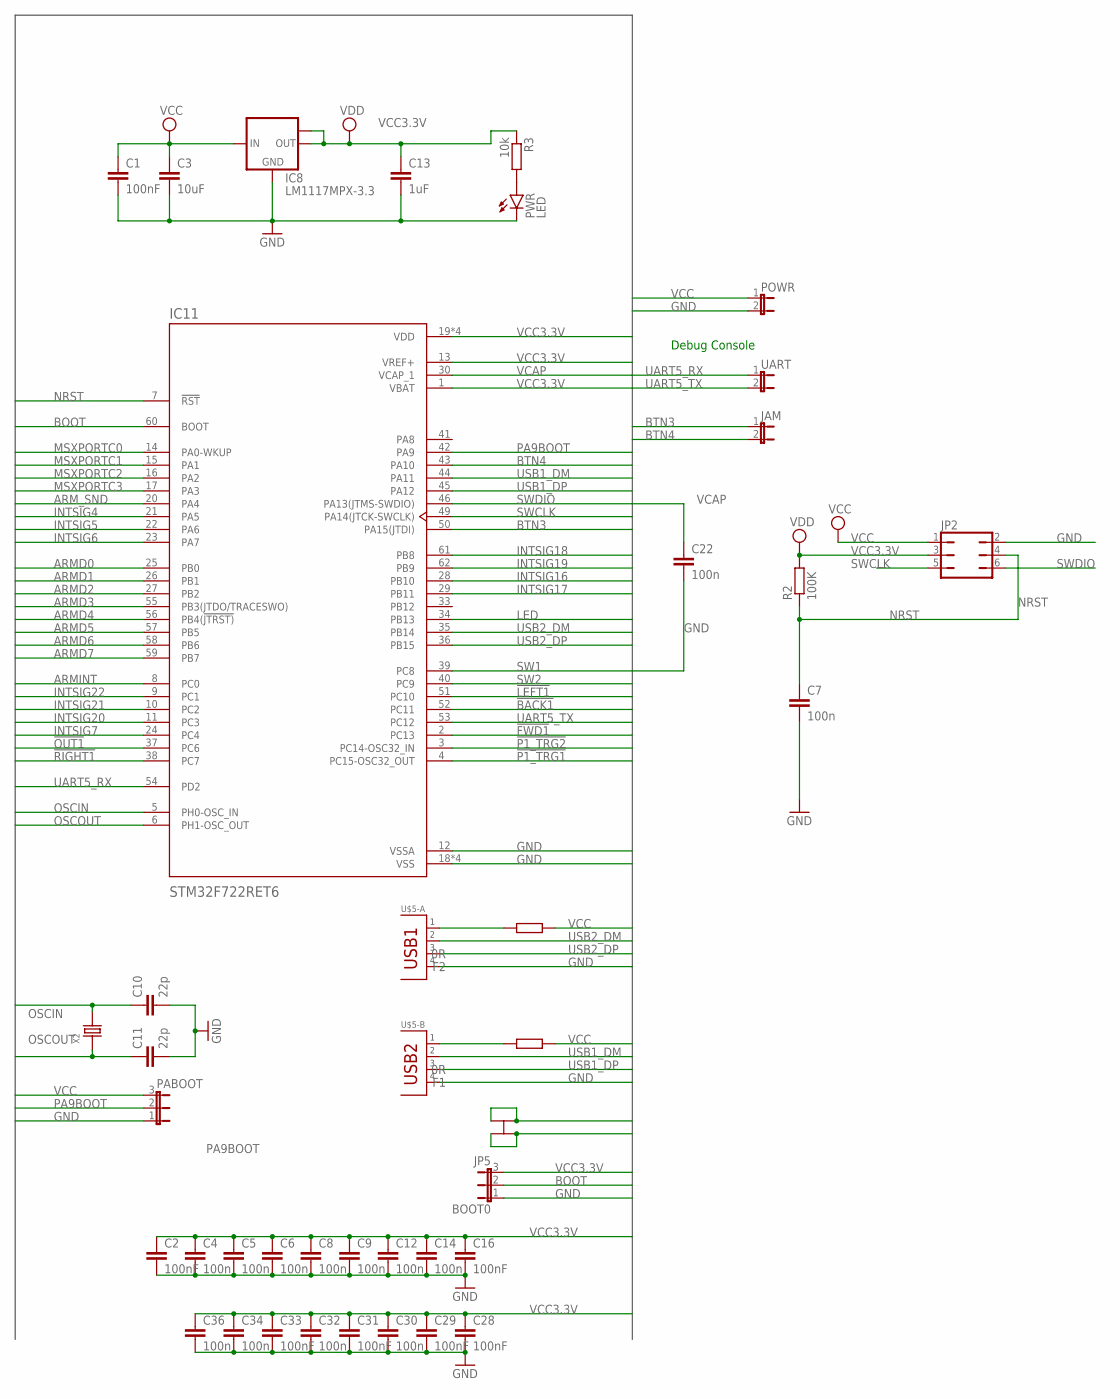
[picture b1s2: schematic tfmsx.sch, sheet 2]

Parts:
BOOT0: JP5; JP2
C1: 100nF; C1206
C2, C16, C28, C29, C31, C33: 100nF; C0603
C3: 10uF; C0603
C4, C5, C6, C7, C8, C9, C12, C14, C30, C32, C34, C36: 100n; C0603
C10, C11: 22p; C0603
C13: 1uF; C1206
C22: 100n; C0805
F1, F2: 0R; R1206
IC8: LM1117MPX-3.3; SOT223
IC11: STM32F722RET6; QFP50P1200X1200X160-64N
JAM: JUMPER-2PTH; 1X02
JP2: JP3Q
PA9BOOT: PABOOT; JP2
POWR: JUMPER-2PTH; 1X02
PWR: LED; SML0805
R2: 100K; M0805
R3: 10k; R0603
U$5: USB-A-2_USB_USB-A-2
UART: JUMPER-2PTH; 1X02
X2: SMD-CRYSTAL-25MHZ-20PF-20PPM(2P-5.0X3.2MM); X2-SMD-5.0X3.2X1.3MM

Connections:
!BACK1: IC11.52 (PC11); also elsewhere on the board
!FWD1: IC11.2 (PC13); also elsewhere on the board
!LEFT1: IC11.51 (PC10); also elsewhere on the board
!OUT1: IC11.37 (PC6); also elsewhere on the board
!P1_TRG1: IC11.4 (PC15-OSC32_OUT); also elsewhere on the board
!P1_TRG2: IC11.3 (PC14-OSC32_IN); also elsewhere on the board
!RIGHT1: IC11.38 (PC7); also elsewhere on the board
ARMD0: IC11.25 (PB0); also elsewhere on the board
ARMD1: IC11.26 (PB1); also elsewhere on the board
ARMD2: IC11.27 (PB2); also elsewhere on the board
ARMD3: IC11.55 (PB3(JTDO/TRACESWO)); also elsewhere on the board
ARMD4: IC11.56 (PB4(!JTRST)); also elsewhere on the board
ARMD5: IC11.57 (PB5); also elsewhere on the board
ARMD6: IC11.58 (PB6); also elsewhere on the board
ARMD7: IC11.59 (PB7); also elsewhere on the board
ARMINT: IC11.8 (PC0); also elsewhere on the board
ARM_SND: IC11.20 (PA4); also elsewhere on the board
BOOT: BOOT0.2, IC11.60 (BOOT)
BTN3: IC11.50 (PA15(JTDI)), JAM.1
BTN4: IC11.43 (PA10), JAM.2
GND: BOOT0.1, C1.2, C2.2, C3.2, C4.2, C5.2, C6.2, C7.2, C8.2, C9.2, C10.2, C11.2, C12.2, C13.2, C14.2, C16.2, C22.2, C28.2, C29.2, C30.2, C31.2, C32.2, C33.2, C34.2, C36.2, IC8.1 (GND), IC11.12 (VSSA), IC11.18 (VSS), IC11.31 (VSS), IC11.47 (VSS), IC11.63 (VSS), JP2.2, PA9BOOT.1, POWR.2, PWR.C, U$5.1-4, U$5.2-4, U$5.SHIELD1, U$5.SHIELD2, U$5.SHIELD3, U$5.SHIELD4; also elsewhere on the board
INTSIG4: IC11.21 (PA5); also elsewhere on the board
INTSIG5: IC11.22 (PA6); also elsewhere on the board
INTSIG6: IC11.23 (PA7); also elsewhere on the board
INTSIG7: IC11.24 (PC4); also elsewhere on the board
INTSIG16: IC11.28 (PB10); also elsewhere on the board
INTSIG17: IC11.29 (PB11); also elsewhere on the board
INTSIG18: IC11.61 (PB8); also elsewhere on the board
INTSIG19: IC11.62 (PB9); also elsewhere on the board
INTSIG20: IC11.11 (PC3); also elsewhere on the board
INTSIG21: IC11.10 (PC2); also elsewhere on the board
INTSIG22: IC11.9 (PC1); also elsewhere on the board
LED: IC11.34 (PB13); also elsewhere on the board
MSXPORTC0: IC11.14 (PA0-WKUP); also elsewhere on the board
MSXPORTC1: IC11.15 (PA1); also elsewhere on the board
MSXPORTC2: IC11.16 (PA2); also elsewhere on the board
MSXPORTC3: IC11.17 (PA3); also elsewhere on the board
unnamed: PWR.A, R3.2
unnamed: F1.2, U$5.2-1
unnamed: F2.2, U$5.1-1
NRST: C7.1, IC11.7 (!RST), JP2.4, R2.1
OSCIN: C10.1, IC11.5 (PH0-OSC_IN), X2.2
OSCOUT: C11.1, IC11.6 (PH1-OSC_OUT), X2.1
PA9BOOT: IC11.42 (PA9), PA9BOOT.2
SW1: IC11.39 (PC8); also elsewhere on the board
SW2: IC11.40 (PC9); also elsewhere on the board
SWCLK: IC11.49 (PA14(JTCK-SWCLK)), JP2.5
SWDIO: IC11.46 (PA13(JTMS-SWDIO)), JP2.6
UART5_RX: IC11.54 (PD2), UART.1
UART5_TX: IC11.53 (PC12), UART.2
USB1_DM: IC11.44 (PA11), U$5.2-2
USB1_DP: IC11.45 (PA12), U$5.2-3
USB2_DM: IC11.35 (PB14), U$5.1-2
USB2_DP: IC11.36 (PB15), U$5.1-3
VCAP: C22.1, IC11.30 (VCAP_1)
VCC: C1.1, C3.1, F1.1, F2.1, IC8.3 (IN), JP2.1, PA9BOOT.3, POWR.1; also elsewhere on the board
VCC3.3V: BOOT0.3, C2.1, C4.1, C5.1, C6.1, C8.1, C9.1, C12.1, C13.1, C14.1, C16.1, C28.1, C29.1, C30.1, C31.1, C32.1, C33.1, C34.1, C36.1, IC8.2 (OUT), IC8.TAB (OUT1), IC11.1 (VBAT), IC11.13 (VREF+), IC11.19 (VDD), IC11.32 (VDD), IC11.48 (VDD), IC11.64 (VDD), JP2.3, R2.2, R3.1; also elsewhere on the board

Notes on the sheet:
Debug Console

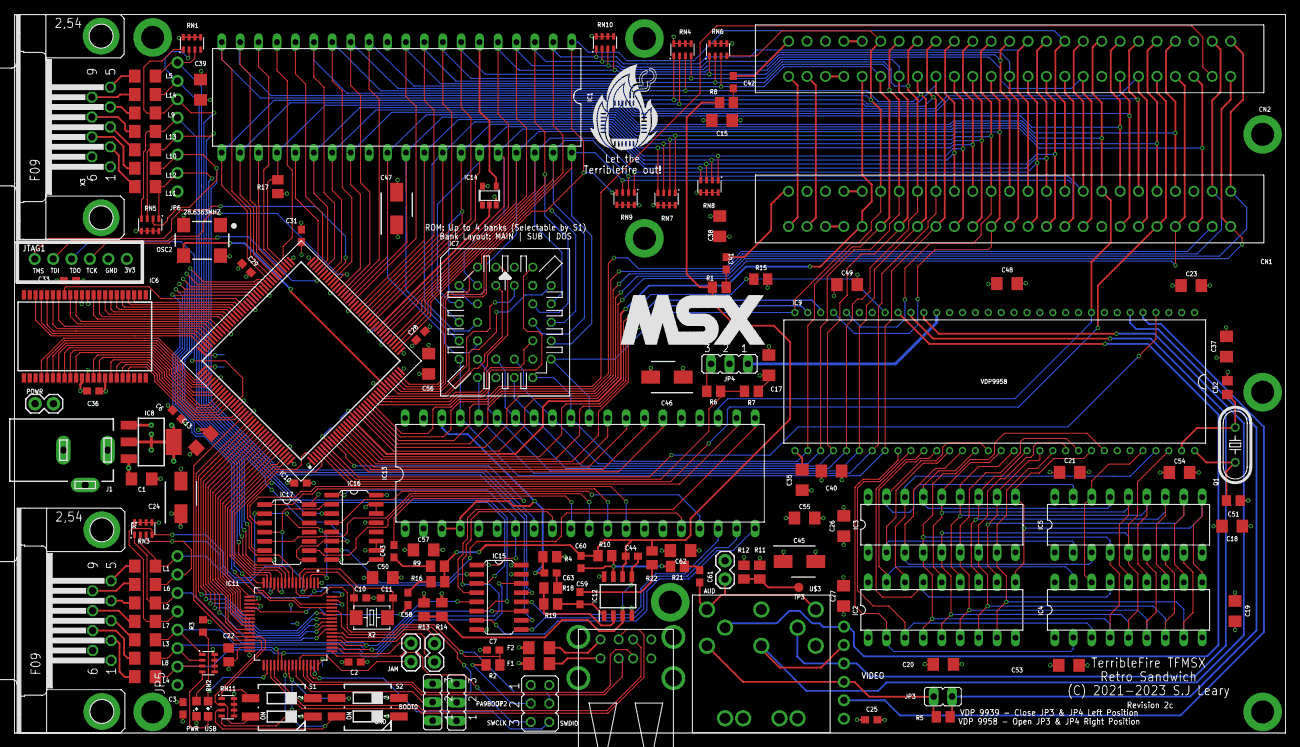
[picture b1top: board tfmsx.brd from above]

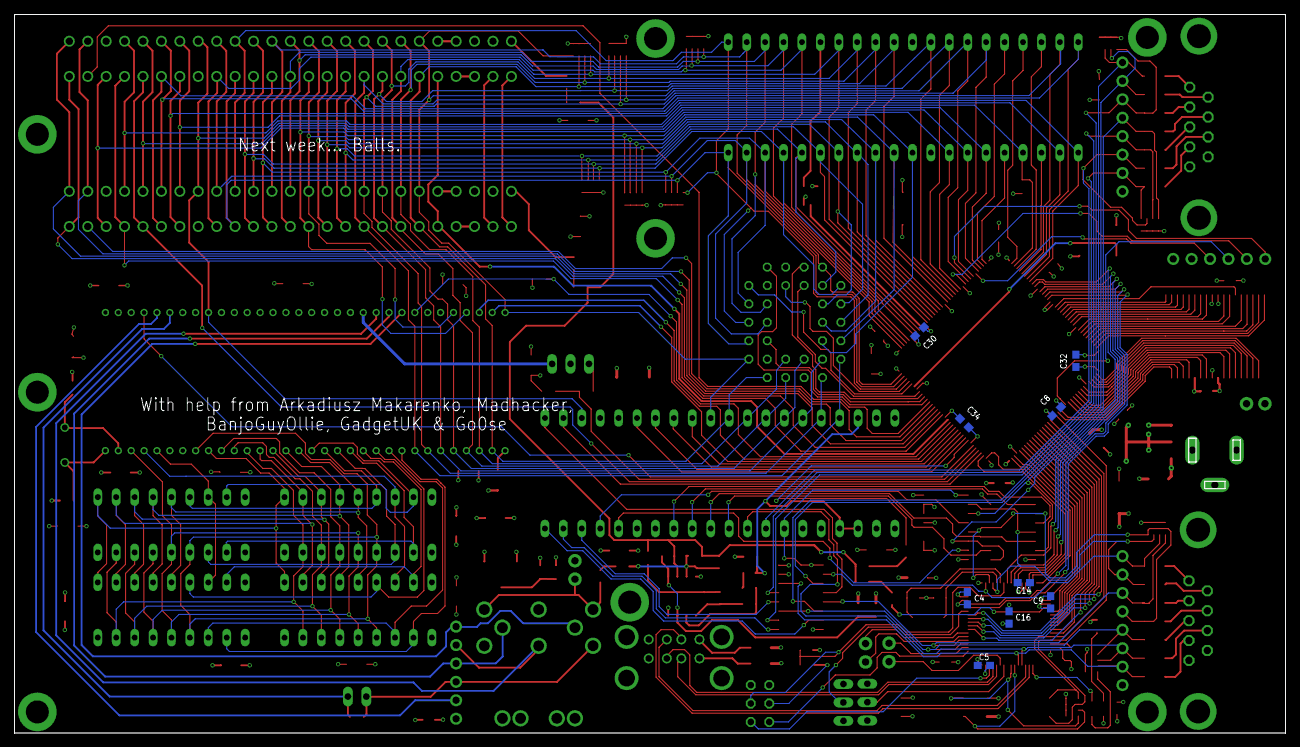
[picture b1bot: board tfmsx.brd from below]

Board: 4 copper layers, 175.3 x 99.1 mm, 156 parts (9 on the bottom side), 238 nets.

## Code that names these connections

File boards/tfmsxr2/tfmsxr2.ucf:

# Copyright (C) 2016-2017, Stephen J. Leary
# All rights reserved.
#
# This file is part of TF530 (Terrible Fire 030 Accelerator)
#
# TF530 is free software: you can redistribute it and/or modify
# it under the terms of the GNU General Public License as published by
# the Free Software Foundation, either version 3 of the License, or
# (at your option) any later version.
#
# TF530 is distributed in the hope that it will be useful,
# but WITHOUT ANY WARRANTY; without even the implied warranty of
# MERCHANTABILITY or FITNESS FOR A PARTICULAR PURPOSE.  See the
# GNU General Public License for more details.
#
# You should have received a copy of the GNU General Public License
# along with TF530. If not, see <http://www.gnu.org/licenses/>.

NET "CLK28M"      LOC="30";
NET "EXCS1"      LOC="21";
NET "EXCS2"      LOC="20";
NET "EXCS12"      LOC="22";
NET "EXSLTSL1"      LOC="23";
NET "EXSLTSL2"      LOC="24";
NET "INT"      LOC="70";
NET "M1"      LOC="66";
NET "RESET"      LOC="69";
NET "RFSH"      LOC="61";
NET "SCE"      LOC="97";
NET "SLOT_INT"      LOC="19";
NET "VDPR"      LOC="14";
NET "VDPW"      LOC="15";
NET "VDP_INT"      LOC="16";
NET "VRESET"      LOC="7";
NET "A<0>"      LOC="58";
NET "A<1>"      LOC="57";
NET "A<2>"      LOC="54";
NET "A<3>"      LOC="52";
NET "A<4>"      LOC="50";
NET "A<5>"      LOC="48";
NET "A<6>"      LOC="45";
NET "A<7>"      LOC="43";
NET "A<8>"      LOC="40";
NET "A<9>"      LOC="38";
NET "A<10>"      LOC="34";
NET "A<11>"      LOC="33";
NET "A<12>"      LOC="35";
NET "A<13>"      LOC="39";
NET "A<14>"      LOC="41";
NET "A<15>"      LOC="44";
NET "PORTB<0>"      LOC="136";
NET "PORTB<1>"      LOC="135";
NET "PORTB<2>"      LOC="134";
NET "PORTB<3>"      LOC="133";
NET "PORTB<4>"      LOC="132";
NET "PORTB<5>"      LOC="131";
NET "PORTB<6>"      LOC="130";
NET "PORTB<7>"      LOC="129";
NET "ARMINT"      LOC="82";
NET "BDIR"      LOC="5";
NET "BUSAK"      LOC="77";
NET "BUSRQ"      LOC="71";

NET "CLKCPU"      LOC="46";
NET "D<0>"      LOC="64";
NET "D<1>"      LOC="68";
NET "D<2>"      LOC="59";
NET "D<3>"      LOC="51";
NET "D<4>"      LOC="49";
NET "D<5>"      LOC="53";
NET "D<6>"      LOC="56";
NET "D<7>"      LOC="60";
NET "HALT"      LOC="76";
NET "INTSIG<4>"      LOC="140";
NET "INTSIG<5>"      LOC="139";
NET "INTSIG<6>"      LOC="138";
NET "INTSIG<7>"      LOC="137";
NET "INTSIG<18>"      LOC="88";
NET "INTSIG<19>"      LOC="87";
NET "INTSIG<20>"      LOC="86";
NET "INTSIG<21>"      LOC="85";
NET "INTSIG<22>"      LOC="83";
NET "IORQ"      LOC="80";
NET "MREQ"      LOC="78";
NET "PORTC<0>"      LOC="3";
NET "PORTC<1>"      LOC="2";
NET "PORTC<2>"      LOC="143";
NET "PORTC<3>"      LOC="142";
NET "NMI"      LOC="74";
NET "PPI_SND"      LOC="9";
NET "PSGCLK"      LOC="4";
NET "RAMSLOT<0>"      LOC="115";
NET "RAMSLOT<1>"      LOC="120";
NET "RAMSLOT<2>"      LOC="121";
NET "RAMSLOT<3>"      LOC="124";
NET "RAMSLOT<4>"      LOC="125";
NET "RD"      LOC="81";
NET "ROMA<14>"      LOC="31";
NET "ROMA<15>"      LOC="28";
NET "ROMA<16>"      LOC="27";
NET "ROMA<17>"      LOC="25";
NET "ROMA<18>"      LOC="32";
NET "ROMOE"      LOC="26";
NET "ROMSEL<0>"      LOC="128";
NET "ROMSEL<1>"      LOC="126";
NET "SA<0>"      LOC="92";
NET "SA<1>"      LOC="93";
NET "SA<2>"      LOC="94";
NET "SA<3>"      LOC="95";
NET "SA<4>"      LOC="96";
NET "SA<5>"      LOC="103";
NET "SA<6>"      LOC="104";
NET "SA<7>"      LOC="105";
NET "SA<8>"      LOC="106";
NET "SA<9>"      LOC="107";
NET "SA<10>"      LOC="110";
NET "SA<11>"      LOC="111";
NET "SA<12>"      LOC="112";
NET "SA<13>"      LOC="113";
NET "SD<0>"      LOC="98";
NET "SD<1>"      LOC="100";
NET "SD<2>"      LOC="101";
NET "SD<3>"      LOC="102";
NET "SD<4>"      LOC="116";
NET "SD<5>"      LOC="117";
NET "SD<6>"      LOC="118";
NET "SD<7>"      LOC="119";
NET "SLOTCLK"      LOC="17";
NET "SWR"      LOC="91";
NET "VDP_SEL"      LOC="6";
NET "WAIT"      LOC="75";
NET "WR"      LOC="79";
NET "YMBC<1>"      LOC="13";
NET "YMBC<2>"      LOC="12";
NET "YMBDIR"      LOC="11";
NET "YMSEL"      LOC="10";

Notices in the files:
eagle/tfmsx.brd:
(C) 2021-2023 S.J Leary
parts and their libraries:
microbuilder: This work is placed in the public domain, and may be freely used for commercial and non-commercial work with the following conditions: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
SparkFun-Retired: Licensing: Creative Commons ShareAlike 4.0 International - https://creativecommons.org/licenses/by-sa/4.0
